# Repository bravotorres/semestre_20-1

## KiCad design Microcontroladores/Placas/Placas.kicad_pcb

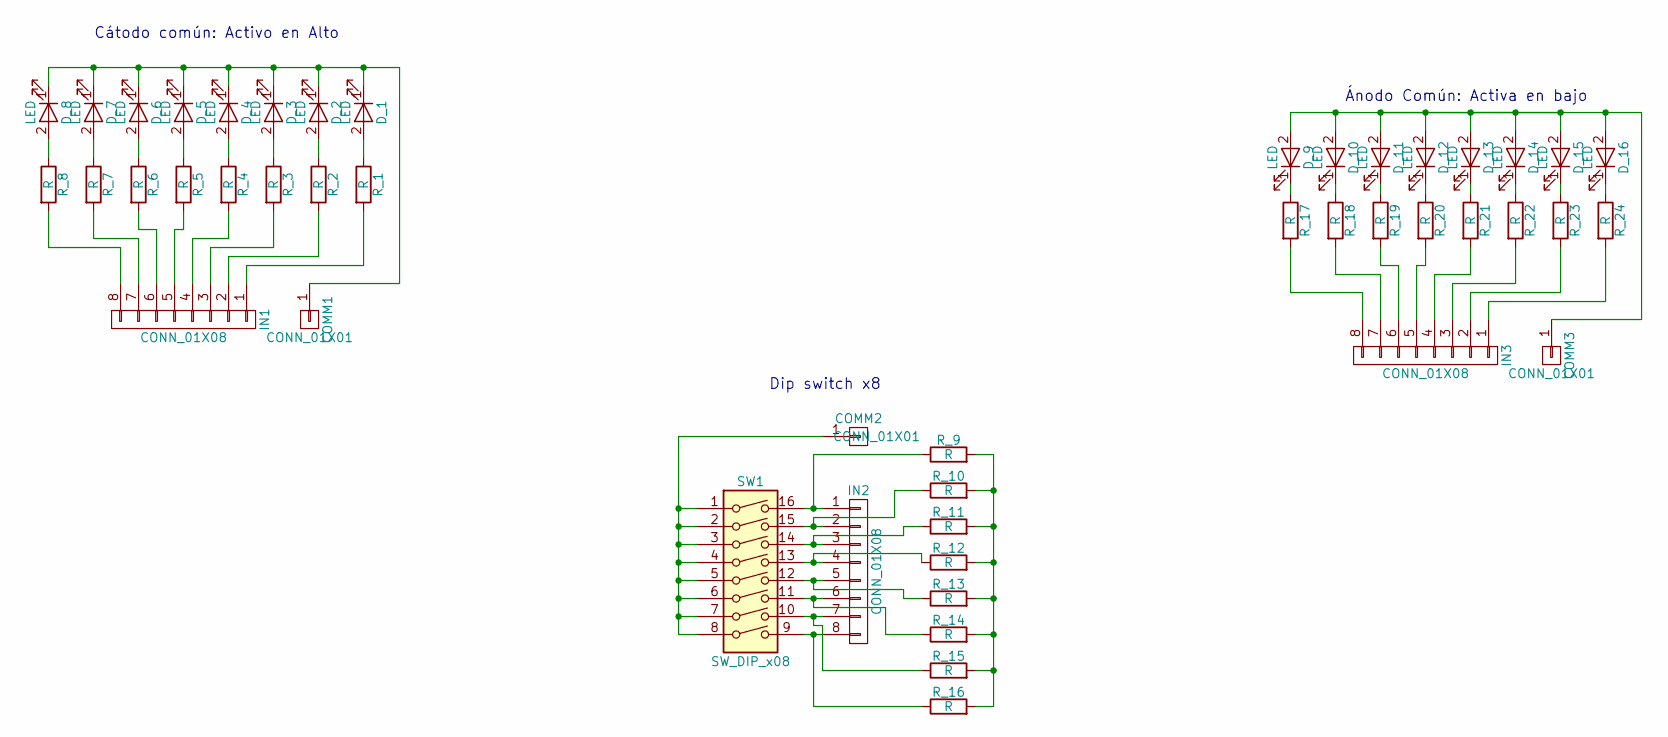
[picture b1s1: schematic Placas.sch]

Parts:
COMM1: CONN_01X01; Pin_Header_Angled_1x01_Pitch2.54mm
COMM2, COMM3: CONN_01X01; Pin_Header_Straight_1x01_Pitch2.54mm
D_1, D_2, D_3, D_4, D_5, D_6, D_7, D_8, D_9, D_10, D_11, D_12, D_13, D_14, D_15, D_16: LED; LED_D5.0mm
IN1: CONN_01X08; Pin_Header_Angled_1x08_Pitch2.54mm
IN2, IN3: CONN_01X08; Pin_Header_Straight_1x08_Pitch2.54mm
R_1, R_2, R_3, R_4, R_5, R_6, R_7, R_8, R_9, R_10, R_11, R_12, R_13, R_14, R_15, R_16, R_17, R_18, R_19, R_20, R_21, R_22, R_23, R_24: R; R_Axial_DIN0207_L6.3mm_D2.5mm_P10.16mm_Horizontal
SW1: SW_DIP_x08; SW_DIP_x8_W7.62mm_Slide

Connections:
unnamed: COMM1.1, D_1.1 (K), D_2.1 (K), D_3.1 (K), D_4.1 (K), D_5.1 (K), D_6.1 (K), D_7.1 (K), D_8.1 (K)
unnamed: COMM2.1, SW1.1, SW1.2, SW1.3, SW1.4, SW1.5, SW1.6, SW1.7, SW1.8
unnamed: COMM3.1, D_9.2 (A), D_10.2 (A), D_11.2 (A), D_12.2 (A), D_13.2 (A), D_14.2 (A), D_15.2 (A), D_16.2 (A)
unnamed: D_1.2 (A), R_1.1
unnamed: D_2.2 (A), R_2.1
unnamed: D_3.2 (A), R_3.1
unnamed: D_4.2 (A), R_4.1
unnamed: D_5.2 (A), R_5.1
unnamed: D_6.2 (A), R_6.1
unnamed: D_7.2 (A), R_7.1
unnamed: D_8.2 (A), R_8.1
unnamed: D_9.1 (K), R_17.1
unnamed: D_10.1 (K), R_18.1
unnamed: D_11.1 (K), R_19.1
unnamed: D_12.1 (K), R_20.1
unnamed: D_13.1 (K), R_21.1
unnamed: D_14.1 (K), R_22.1
unnamed: D_15.1 (K), R_23.1
unnamed: D_16.1 (K), R_24.1
unnamed: IN1.1, R_1.2
unnamed: IN1.2, R_2.2
unnamed: IN1.3, R_3.2
unnamed: IN1.4, R_4.2
unnamed: IN1.5, R_5.2
unnamed: IN1.6, R_6.2
unnamed: IN1.7, R_7.2
unnamed: IN1.8, R_8.2
unnamed: IN2.1, R_9.1, SW1.16
unnamed: IN2.2, R_10.1, SW1.15
unnamed: IN2.3, R_11.1, SW1.14
unnamed: IN2.4, R_12.1, SW1.13
unnamed: IN2.5, R_13.1, SW1.12
unnamed: IN2.6, R_14.1, SW1.11
unnamed: IN2.7, R_15.1, SW1.10
unnamed: IN2.8, R_16.1, SW1.9
unnamed: IN3.1, R_24.2
unnamed: IN3.2, R_23.2
unnamed: IN3.3, R_22.2
unnamed: IN3.4, R_21.2
unnamed: IN3.5, R_20.2
unnamed: IN3.6, R_19.2
unnamed: IN3.7, R_18.2
unnamed: IN3.8, R_17.2
unnamed: R_9.2, R_10.2, R_11.2, R_12.2, R_13.2, R_14.2, R_15.2, R_16.2

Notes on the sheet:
Cátodo común: Activo en Alto
Ánodo Común: Activa en bajo
Dip switch x8

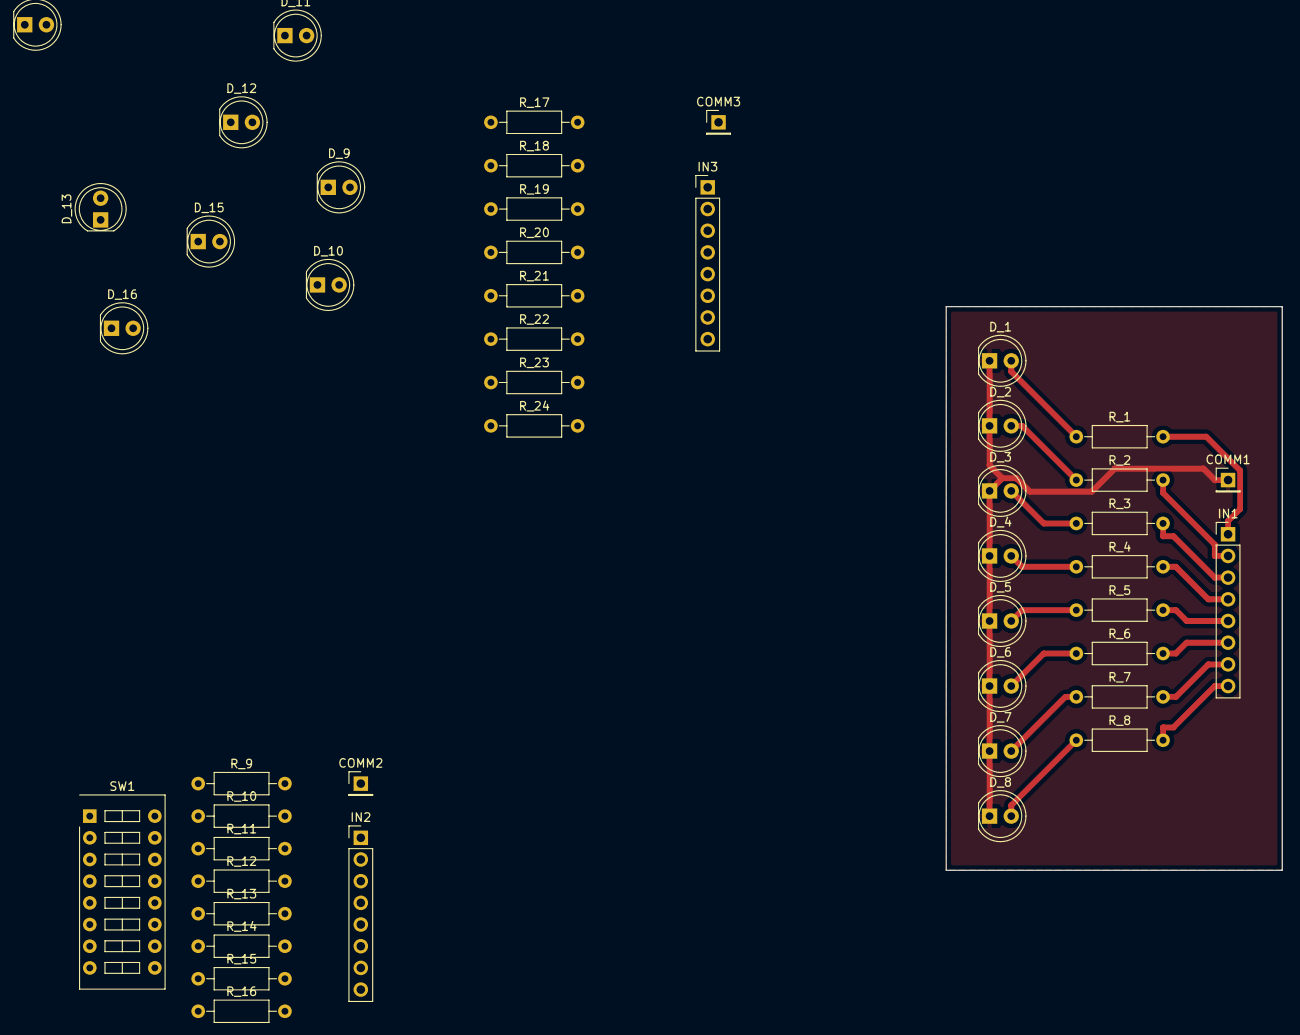
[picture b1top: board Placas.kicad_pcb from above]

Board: 2 copper layers, 39.4 x 66.0 mm, 47 parts (0 on the bottom side), 44 nets.

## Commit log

2019-08-19 [Instrumentacion]: Integración de Archivos.
    intento de Simulación e Linux sobre la Práctica No.1
2019-08-29 Add simulation files. Error
2019-09-02 Practica No.2
2019-09-05 Placas de Leds para Microcontroladores.
2019-09-09 Placas de Leds 01 Para imprimir.
2019-09-17 Add Placas
2019-09-17 Update Laptop Icarus
2019-10-14 [Instrumentacion] Add Practice No.05
2019-10-16 []Actualización
2019-10-16 [Instrumentación] Actaulizacion de Practica 5
2019-12-29 Project...
